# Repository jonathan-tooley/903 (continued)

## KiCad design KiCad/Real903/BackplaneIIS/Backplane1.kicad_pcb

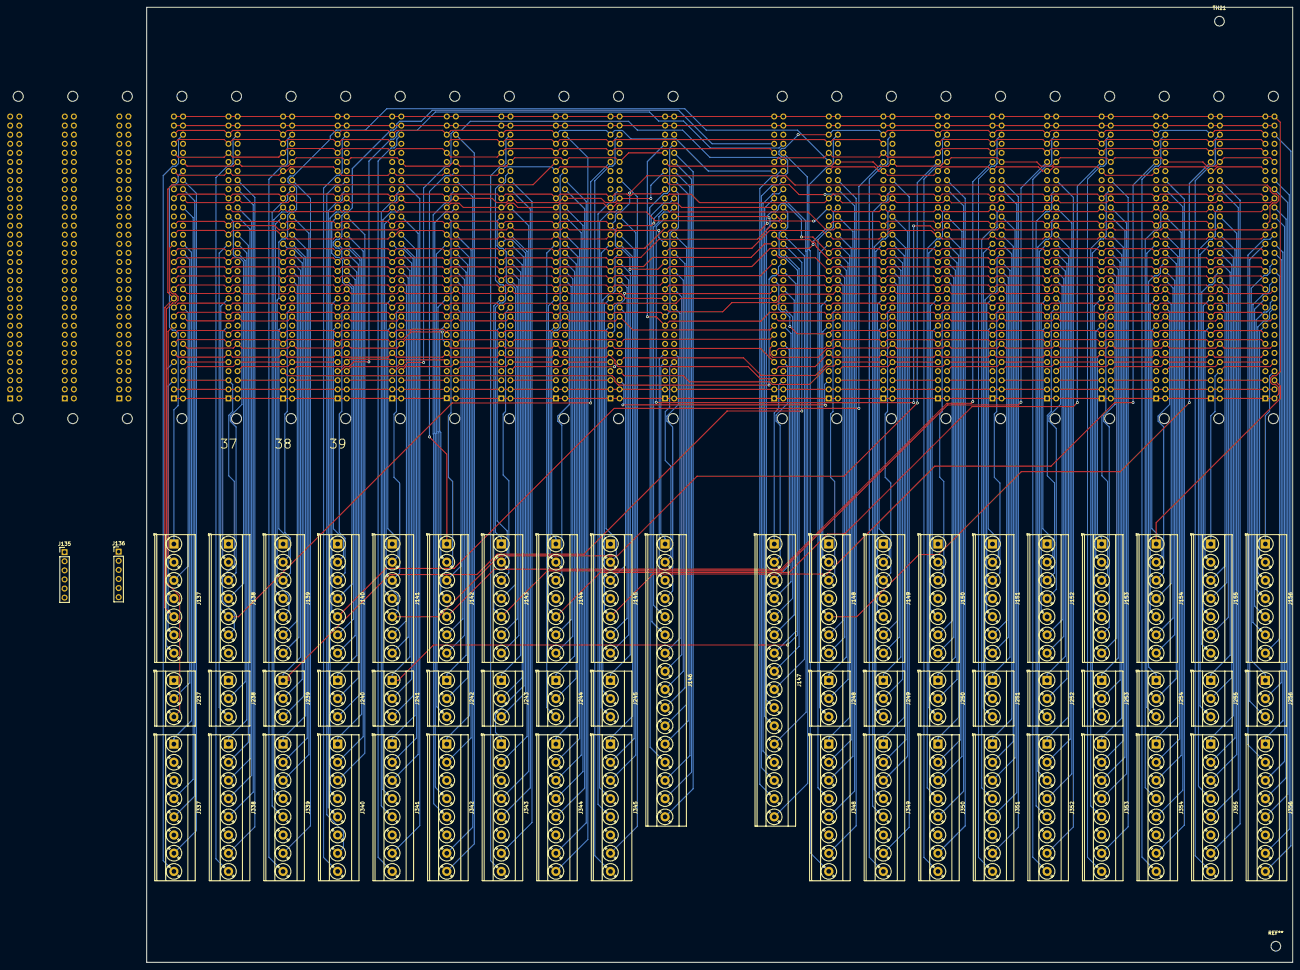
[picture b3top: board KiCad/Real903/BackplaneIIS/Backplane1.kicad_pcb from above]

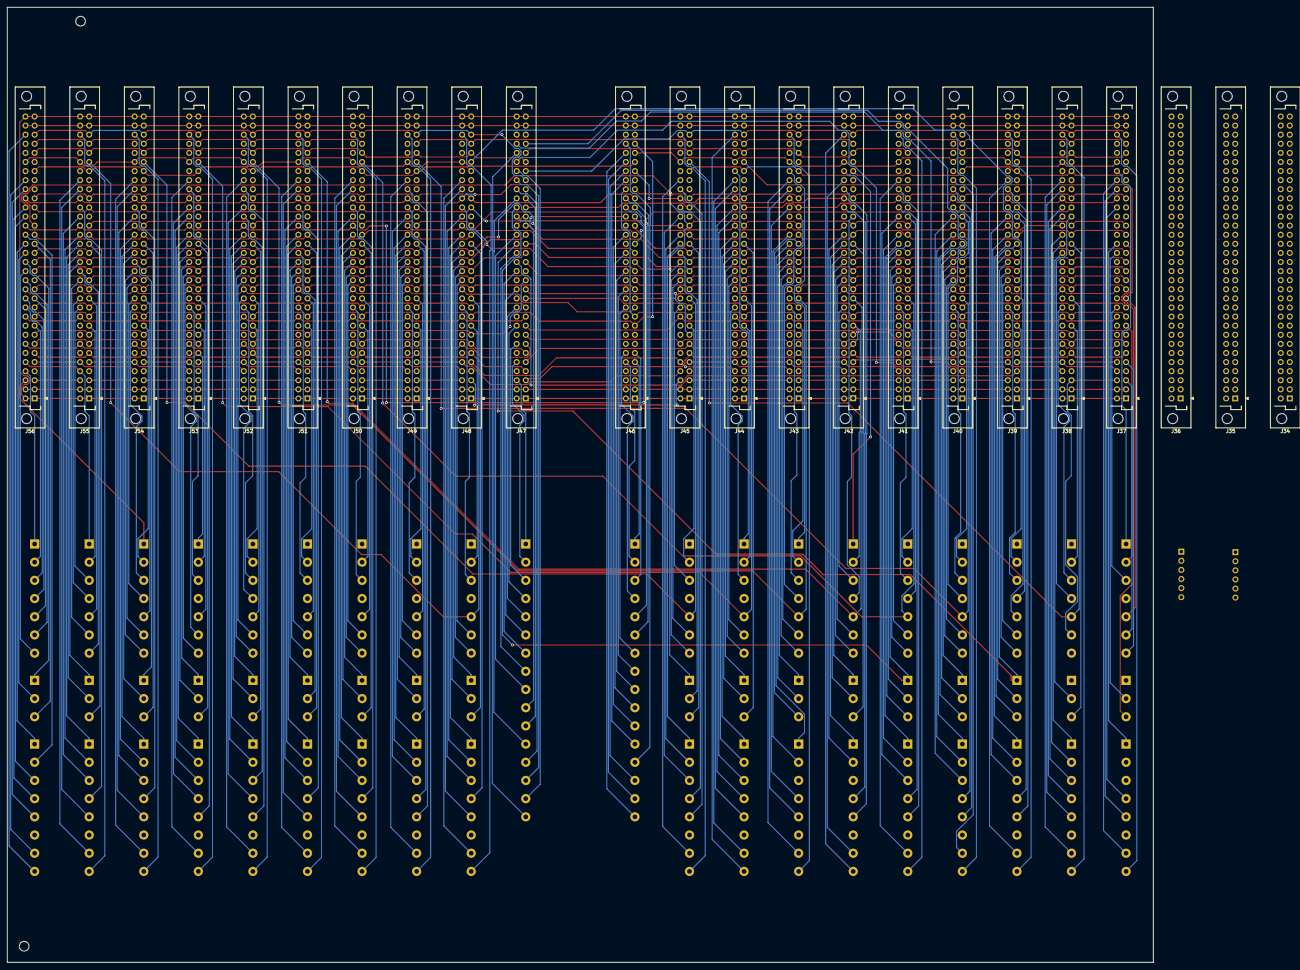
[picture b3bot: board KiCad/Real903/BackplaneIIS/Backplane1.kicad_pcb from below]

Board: 2 copper layers, 320.0 x 266.7 mm, 82 parts (23 on the bottom side), 447 nets.

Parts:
J34, J35, J36, J37, J38, J39, J40, J41, J42, J43, J44, J45, J46, J47, J48, J49, J50, J51, J52, J53, J54, J55, J56: DIN41612_B_2x32_Vertical
J135, J136: PinHeader_1x06_P2.54mm_Vertical
J137, J138, J139, J140, J141, J142, J143, J144, J145, J148, J149, J150, J151, J152, J153, J154, J155, J156: TerminalBlock_Phoenix_MKDS-3-7-5.08_1x07_P5.08mm_Horizontal
J146, J147: TerminalBlock_Phoenix_MKDS-3-16-5.08_1x16_P5.08mm_Horizontal
J237, J238, J239, J240, J241, J242, J243, J244, J245, J248, J249, J250, J251, J252, J253, J254, J255, J256: TerminalBlock_Phoenix_MKDS-3-3-5.08_1x03_P5.08mm_Horizontal
J337, J338, J339, J340, J341, J342, J343, J344, J345, J348, J349, J350, J351, J352, J353, J354, J355, J356: TerminalBlock_Phoenix_MKDS-3-8-5.08_1x08_P5.08mm_Horizontal
TH21: MountingHole_2.7mm

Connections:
0TM1-: J46.15, J48.20, J49.20, J50.20, J51.20, J52.20, J53.20, J54.20, J55.20
0TM2-: J37.20, J38.20, J39.20, J40.20, J41.20, J42.20, J43.20, J44.20, J45.20, J46.16, J56.20
6v: J34.2, J34.B, J35.2, J35.B, J36.2, J36.B, J37.2, J37.B, J38.2, J38.B, J39.2, J39.B, J40.2, J40.B, J41.2, J41.B, J42.2, J42.B, J43.2, J43.B, J44.2, J44.B, J45.2, J45.B, J46.2, J46.B, J47.2, J47.B, J48.2, J48.B, J49.2, J49.B, J50.2, J50.B, J51.2, J51.B, J52.2, J52.B, J53.2, J53.B, J54.2, J54.B, J55.2, J55.B, J56.2, J56.B
/RegistersA/C10: J44.C, J45.3
/RegistersA/C11: J43.C, J44.3
/RegistersA/C12: J42.C, J43.3
/RegistersA/C13: J41.C, J42.3
/RegistersA/C14: J40.C, J41.3
/RegistersA/C15: J39.C, J40.3
/RegistersA/C16: J38.C, J39.3
/RegistersB/C1: J55.C, J56.3
/RegistersB/C2: J54.C, J55.3
/RegistersB/C3: J53.C, J54.3
/RegistersB/C4: J52.C, J53.3
/RegistersB/C5: J51.C, J52.3
/RegistersB/C6: J50.C, J51.3
/RegistersB/C7: J49.C, J50.3
/RegistersB/C8: J48.C, J49.3
A1-: J56.AB, J356.5
A2: J48.12, J55.27, J148.5
A2-: J55.AB, J355.5
A3: J45.12, J54.27, J145.5
A3-: J54.AB, J354.5
A4: J44.12, J53.27, J144.5
A4-: J53.AB, J353.5
A5: J43.12, J52.27, J143.5
A5-: J52.AB, J352.5
A6: J42.12, J51.27, J142.5
A6-: J51.AB, J351.5
A7: J41.12, J50.27, J141.5
A7-: J50.AB, J350.5
A8: J40.12, J49.27, J140.5
A8-: J49.AB, J349.5
A9: J39.12, J48.27, J139.5
A9-: J48.AB, J348.5
A10: J38.12, J45.27, J138.5
A10-: J45.AB, J345.5
A11: J37.12, J44.27, J137.5
A11-: J44.AB, J344.5
A12-: J43.AB, J343.5
A13-: J42.AB, J342.5
A14-: J41.AB, J341.5
A15-: J40.AB, J340.5
A16-: J39.AB, J339.5
A17-: J38.AB, J338.5
A18-: J37.AB, J337.5
ATF1: J47.27, J48.28, J49.28, J50.28, J51.28, J52.28, J53.28, J54.28, J55.28, J56.28
ATF2: J37.28, J38.28, J39.28, J40.28, J41.28, J42.28, J43.28, J44.28, J45.28, J47.28
ATFa: J47.AC, J147.14
C9: J45.C, J48.3
C17: J37.C, J38.3, J138.6
C18: J37.3, J137.6
CRS: J46.5, J146.1
CRSm: J46.E, J146.2
DTF1-1: J50.29, J51.29, J52.29, J53.29, J54.29, J55.29, J56.29
DTF1-2: J42.29, J43.29, J44.29, J45.29, J48.29, J49.29
DTF2a: J37.29, J38.29, J39.29, J40.29, J41.29
ETJ2-: J55.N, J155.4
ETJ3-: J54.N, J154.4
F1: J55.D, J56.E, J155.1
F2: J54.D, J55.E, J56.5
F3: J53.D, J54.E, J55.5
F4: J52.D, J53.E, J54.5
F5: J51.D, J52.E, J53.5
F6: J50.D, J51.E, J52.5
F7: J49.D, J50.E, J51.5
F8: J48.D, J49.E, J50.5
F9: J45.D, J48.E, J49.5
F10: J44.D, J45.E, J48.5
F11: J43.D, J44.E, J45.5
F12: J42.D, J43.E, J44.5
F13: J41.D, J42.E, J43.5
F14: J40.D, J41.E, J42.5
F15: J39.D, J40.E, J41.5
F16: J38.D, J39.E, J40.5
F17: J37.D, J38.E, J39.5
F18: J37.E, J38.5
FTG1: J47.4, J48.6, J49.6, J50.6, J51.6, J52.6, J53.6, J54.6, J55.6, J56.6, J153.1
FTG2: J37.6, J38.6, J39.6, J40.6, J41.6, J42.6, J43.6, J44.6, J45.6, J47.3
FTGa: J47.C, J147.1
GND: J34.1, J34.32, J34.A, J34.AL, J35.1, J35.32, J35.A, J35.AL, J36.1, J36.32, J36.A, J36.AL, J37.1, J37.32, J37.A, J37.AL, J38.1, J38.32, J38.A, J38.AL, J39.1, J39.32, J39.A, J39.AL, J40.1, J40.32, J40.A, J40.AL, J41.1, J41.32, J41.A, J41.AL, J42.1, J42.32, J42.A, J42.AL, J43.1, J43.32, J43.A, J43.AL, J44.1, J44.32, J44.A, J44.AL, J45.1, J45.32, J45.A, J45.AL, J46.1, J46.32, J46.A, J46.AL, J47.1, J47.32, J47.A, J47.AL, J48.1, J48.32, J48.A, J48.AL, J49.1, J49.32, J49.A, J49.AL, J50.1, J50.32, J50.A, J50.AL, J51.1, J51.32, J51.A, J51.AL, J52.1, J52.32, J52.A, J52.AL, J53.1, J53.32, J53.A, J53.AL, J54.1, J54.32, J54.A, J54.AL, J55.1, J55.32, J55.A, J55.AL, J56.1, J56.32, J56.A, J56.AL
GTA1: J46.23, J48.23, J49.23, J50.23, J51.23, J52.23, J53.23, J54.23, J55.23, J56.23
GTA2: J37.23, J38.23, J39.23, J40.23, J41.23, J42.23, J43.23, J44.23, J45.23, J46.24
GTAa: J46.AA, J146.6
GTJ1: J46.13, J48.13, J49.13, J50.13, J51.13, J52.13, J53.13, J54.13, J55.13, J56.13
GTJ2: J37.13, J38.13, J39.13, J40.13, J41.13, J42.13, J43.13, J44.13, J45.13, J46.14
GTJa: J46.P, J146.8
GTM1: J46.19, J48.17, J49.17, J50.17, J51.17, J52.17, J53.17, J54.17, J55.17, J56.17
GTM2: J37.17, J38.17, J39.17, J40.17, J41.17, J42.17, J43.17, J44.17, J45.17, J46.20
GTMa: J46.W, J146.11
GTQ1: J46.27, J48.AE, J49.AE, J50.AE, J51.AE, J52.AE, J53.AE, J54.AE, J55.AE, J56.AE
GTQ2: J37.AE, J38.AE, J39.AE, J40.AE, J41.AE, J42.AE, J43.AE, J44.AE, J45.AE, J46.28
GTQa: J46.AC, J146.12
I1: J41.21, J141.4
I1-: J41.W, J341.2
I2: J40.21, J140.4
I2-: J40.W, J340.2
I3: J39.21, J139.4
I3-: J39.W, J339.2
I4: J38.21, J138.4
I4-: J38.W, J338.2
II1: J34.13, J56.25
II1m: J34.P, J35.P, J36.P
II2: J34.14, J55.25
II2m: J34.R, J35.R, J36.R
II3: J34.15, J54.25
II3m: J34.S, J35.S, J36.S
II4: J34.16, J53.25
II4m: J34.T, J35.T, J36.T
II5: J34.17, J52.25
II5m: J34.U, J35.U, J36.U
II6: J34.18, J51.25
II6m: J34.V, J35.V, J36.V
II7: J34.19, J50.25
II7m: J34.W, J35.W, J36.W
II8: J34.20, J49.25
II8m: J34.X, J35.X, J36.X
II9: J34.21, J48.25
II9m: J34.Y, J35.Y, J36.Y
II10: J34.22, J45.25
II10m: J34.Z, J35.Z, J36.Z
II11: J34.23, J44.25
II11m: J34.AA, J35.AA, J36.AA
II12: J34.24, J43.25
II12m: J34.AB, J35.AB, J36.AB
II13: J34.25, J42.25
II13m: J34.AC, J35.AC, J36.AC
II14: J34.26, J41.25
II14m: J34.AD, J35.AD, J36.AD
II15: J34.27, J40.25
II15m: J34.AE, J35.AE, J36.AE
II16: J34.28, J39.25
II16m: J34.AF, J35.AF, J36.AF
II17: J34.12, J38.25
II17m: J34.N, J35.AH, J36.AH
II18: J34.30, J37.25
II18m: J34.AJ, J35.AJ, J36.AJ
IIG: J35.26, J36.26
IIG-: J36.9, J136.2
IIS: J35.15, J36.8, J136.1
IP1: J56.9, J156.2
IP2: J55.9, J155.2
IP3: J54.9, J154.2
IP4: J53.9, J153.2
IP5: J52.9, J152.2
IP6: J51.9, J151.2
IP7: J50.9, J150.2
IP8: J49.9, J149.2
IP9: J48.9, J148.2
IP10: J45.9, J145.2
IP11: J44.9, J144.2
IP12: J43.9, J143.2
IP13: J42.9, J142.2
IP14: J41.9, J141.2
IP15: J40.9, J140.2
IP16: J39.9, J139.2
IP17: J38.9, J138.2
IP18: J37.9, J137.2
IP'1: J56.12, J156.5
IP'2: J55.12, J155.5
IP'3: J54.12, J154.5
IP'4: J53.12, J153.5
IP'5: J52.12, J152.5
IP'6: J51.12, J151.5
IP'7: J50.12, J150.5
IP'8: J49.12, J149.5
ITF: J56.C, J154.1
J1: J56.T, J256.1
J1': J35.7, J36.7, J135.2
J1-: J56.R, J156.6
J1-': J35.8, J135.1
J2: J55.T, J255.1
J2': J35.9, J135.4
J2-: J55.R, J155.6
J2-': J35.10, J36.10, J135.3
J3: J54.T, J254.1
J3': J35.11, J36.11, J135.6
J3-: J54.R, J154.6
J3-': J35.12, J36.C, J135.5
J4: J35.14, J53.T, J253.1
J4-: J35.13, J36.12, J53.R, J153.6
J5: J36.13, J52.T, J252.1
J5-: J52.R, J152.6
J6: J36.14, J51.T, J251.1
J6-: J51.R, J151.6
J7: J36.15, J50.T, J250.1
J7-: J50.R, J150.6
J8: J36.18, J49.T, J249.1
J8-: J49.R, J149.6
J9: J36.19, J48.T, J248.1
J9-: J48.R, J148.6
J10: J36.20, J45.T, J245.1
J10-: J45.R, J145.6
J11: J36.21, J44.T, J244.1
J11-: J44.R, J144.6
J12: J36.22, J43.T, J243.1
J12-: J43.R, J143.6
J13: J36.23, J42.T, J242.1
J13-: J42.R, J142.6
J14: J41.T, J47.Z, J241.1
J14-: J36.24, J41.R, J141.6
J15: J40.T, J47.29, J240.1
J15-: J36.25, J40.R, J140.6
J16: J39.T, J47.V, J239.1
J16-: J36.29, J39.R, J139.6
JTF1: J47.15, J48.14, J49.14, J50.14, J51.14, J52.14, J53.14, J54.14, J55.14, J56.14
JTF2: J37.14, J38.14, J39.14, J40.14, J41.14, J42.14, J43.14, J44.14, J45.14, J47.16
JTFa: J47.S, J147.7
JTG14-: J41.4, J47.AE
JTG15-: J40.4, J47.AH
JTG16-: J39.4, J47.T
JTPC: J47.23, J47.24, J147.11
JTPCa: J47.AA, J147.12
KTJ1-: J56.N, J156.4
KTJ5-: J52.N, J152.4
LTG1: J47.7, J48.H, J49.H, J50.H, J51.H, J52.H, J53.H, J54.H, J55.H, J56.H
LTG2: J37.H, J38.H, J39.H, J40.H, J41.H, J42.H, J43.H, J44.H, J45.H, J47.8
LTGa: J47.H, J147.3
M1-: J56.V, J356.1
M2-: J55.V, J355.1
M3-: J54.V, J354.1
M4-: J53.V, J353.1
M5-: J52.V, J352.1
M6-: J51.V, J351.1
M7-: J50.V, J350.1
M8-: J49.V, J349.1
M9-: J48.V, J348.1
M10-: J45.V, J345.1
M11: J44.AD, J144.1
M11-: J44.V, J344.1
M12: J43.AD, J143.1
M12-: J43.V, J343.1
M13: J42.AD, J142.1
M13-: J42.V, J342.1
M14-: J41.V, J341.1
M15-: J40.V, J340.1
M16-: J39.V, J339.1
M17-: J38.V, J338.1
M18: J37.AD, J137.1
M18-: J37.V, J337.1
M-TF1: J47.19, J48.16, J49.16, J50.16, J51.16, J52.16, J53.16, J54.16, J55.16, J56.16
M-TF2: J37.16, J38.16, J39.16, J40.16, J41.16, J42.16, J43.16, J44.16, J45.16, J47.20
M-TFa: J47.W, J147.9
MTF1: J47.17, J48.15, J49.15, J50.15, J51.15, J52.15, J53.15, J54.15, J55.15, J56.15
MTF2: J37.15, J38.15, J39.15, J40.15, J41.15, J42.15, J43.15, J44.15, J45.15, J47.18
MTFa: J47.U, J147.8
MTI: J38.22, J39.22, J40.22, J41.22, J47.X
MTP1: J47.21, J48.22, J49.22, J50.22, J51.22, J52.22, J53.22, J54.22, J55.22, J56.22
MTP2: J42.22, J43.22, J44.22, J45.22, J47.22
MTPa: J46.Y, J47.Y, J147.10
Neg6v: J34.31, J34.AK, J35.31, J35.AK, J36.31, J36.AK, J37.31, J37.AK, J38.31, J38.AK, J39.31, J39.AK, J40.31, J40.AK, J41.31, J41.AK, J42.31, J42.AK, J43.31, J43.AK, J44.31, J44.AK, J45.31, J45.AK, J46.31, J46.AK, J47.31, J47.AK, J48.31, J48.AK, J49.31, J49.AK, J50.31, J50.AK, J51.31, J51.AK, J52.31, J52.AK, J53.31, J53.AK, J54.31, J54.AK, J55.31, J55.AK, J56.31, J56.AK
OTA1-: J46.25, J48.AA, J49.AA, J50.AA, J51.AA, J52.AA, J53.AA, J54.AA, J55.AA, J56.AA
OTA2-: J37.AA, J38.AA, J39.AA, J40.AA, J41.AA, J42.AA, J43.AA, J44.AA, J45.AA, J46.26
OTA-': J46.Z, J146.5
OTG1-: J46.9, J46.29, J48.10, J49.10, J50.10, J51.10, J52.10, J53.10, J54.10, J55.10, J56.10
OTG2-: J37.10, J38.10, J39.10, J40.10, J41.10, J42.10, J43.10, J44.10, J45.10, J46.10, J46.AB
OTI-: J38.X, J39.X, J40.X, J41.X
OTJ1-: J46.11, J48.P, J49.P, J50.P, J51.P, J52.P, J53.P, J54.P, J55.P, J56.P
OTJ2-: J37.P, J38.P, J39.P, J40.P, J41.P, J42.P, J43.P, J44.P, J45.P, J46.12
OTJ-: J46.M, J146.7
OTMa: J46.S, J146.9
OTP1-: J46.21, J50.X, J51.X, J52.X, J53.X, J54.X, J55.X, J56.X
OTP2-: J42.X, J43.X, J44.X, J45.X, J46.22, J48.X, J49.X
OTQ1-: J48.26, J49.26, J50.26, J51.26, J52.26, J53.26, J54.26, J55.26, J56.26
OTQ2-: J37.26, J38.26, J39.26, J40.26, J41.26, J42.26, J43.26, J44.26, J45.26
P1-: J56.W, J356.2
P2-: J55.W, J355.2
P3-: J54.W, J354.2
P4-: J53.W, J353.2
P5-: J52.W, J352.2
P6-: J51.W, J351.2
P7-: J50.W, J350.2
P8-: J49.W, J349.2
P9-: J48.W, J348.2
P10-: J45.W, J345.2
P11-: J44.W, J344.2
P12: J43.21, J143.4
P12-: J43.W, J343.2
P13: J42.21, J142.4
P13-: J42.W, J342.2
PTG1-1: J47.10, J48.L, J49.L, J50.L, J51.L, J52.L, J53.L, J54.L, J55.L, J56.L
PTG1-2: J37.L, J38.L, J39.L, J40.L, J41.L, J42.L, J43.L, J44.L, J45.L, J47.9
PTG1-a: J47.K, J147.4
PTG2-1: J47.11, J48.11, J49.11, J50.11, J51.11, J52.11, J53.11, J54.11, J55.11, J56.11
PTG2-2: J37.11, J38.11, J39.11, J40.11, J41.11, J42.11, J43.11, J44.11, J45.11, J47.12
PTG2-a: J47.M, J147.5
QTF1: J47.25, J48.30, J49.30, J50.30, J51.30, J52.30, J53.30, J54.30, J55.30, J56.30
QTF2: J37.30, J38.30, J39.30, J40.30, J41.30, J42.30, J43.30, J44.30, J45.30, J47.26
QTFa: J47.AB, J147.13
RESET2-: J46.AH, J146.13
RTG1: J47.6, J48.7, J49.7, J50.7, J51.7, J52.7, J53.7, J54.7, J55.7, J56.7
RTG2: J37.7, J38.7, J39.7, J40.7, J41.7, J42.7, J43.7, J44.7, J45.7, J47.5
RTGa: J47.E, J147.2
SFD: J46.6, J146.3
SFDm: J46.F, J146.4
SKT1AA: J44.AC, J344.7
SKT1B: J56.M, J156.3
SKT1BB: J43.AC, J343.7
SKT1C: J55.M, J155.3
SKT1CC: J42.AC, J342.7
SKT1D: J54.M, J154.3
SKT1DD: J41.AC, J341.7
SKT1E: J53.M, J153.3
SKT1EE: J40.AC, J340.7
SKT1F: J52.M, J152.3
SKT1FF: J39.AC, J339.7
SKT1G: J51.M, J151.3
SKT1GG: J38.AC, J338.7
SKT1H: J50.M, J150.3
SKT1HH: J37.AC, J337.7
SKT1J: J49.M, J149.3
SKT1K: J48.M, J148.3
SKT1L: J45.M, J145.3
SKT1M: J44.M, J144.3
SKT1N: J43.M, J143.3
SKT1P: J42.M, J142.3
SKT1R: J41.M, J141.3
SKT1S: J40.M, J140.3
SKT1T: J39.M, J139.3
SKT1U: J38.M, J138.3
SKT1V: J37.M, J137.3
SKT1W: J56.Z, J356.4
SKT1X: J55.Z, J355.4
SKT1Y: J54.Z, J354.4
SKT1Z: J53.Z, J353.4
SKT1a: J52.Z, J352.4
SKT1b_: J51.Z, J351.4
SKT1c_: J50.Z, J350.4
SKT1d_: J49.Z, J349.4
SKT1e_: J48.Z, J348.4
SKT1f_: J45.Z, J345.4
SKT1g_: J44.Z, J344.4
SKT1h_: J43.Z, J343.4
SKT1i: J42.Z, J342.4
SKT1j_: J41.Z, J341.4
SKT1k_: J40.Z, J340.4
SKT1m_: J39.Z, J339.4
SKT1n_: J38.Z, J338.4
SKT1p_: J37.Z, J337.4
SKT1q: J56.AC, J356.7
SKT1r_: J55.AC, J355.7
SKT1s_: J54.AC, J354.7
SKT1t_: J53.AC, J353.7
SKT1u_: J52.AC, J352.7
SKT1v_: J51.AC, J351.7
SKT1w_: J50.AC, J350.7
SKT1x_: J49.AC, J349.7
SKT1y_: J48.AC, J348.7
SKT1z_: J45.AC, J345.7
SKT2B: J56.U, J256.2
SKT2C: J55.U, J255.2
SKT2D: J54.U, J254.2
SKT2E: J53.U, J253.2
SKT2F: J52.U, J252.2
SKT2G: J51.U, J251.2
SKT2H: J50.U, J250.2
SKT2J: J49.U, J249.2
SKT2K: J48.U, J248.2
SKT2L: J45.U, J245.2
SKT2M: J44.U, J244.2
SKT2N: J43.U, J243.2
SKT2P: J42.U, J242.2
SKT2R: J41.U, J241.2
SKT2S: J40.U, J240.2
SKT2T: J39.U, J239.2
SKT2U: J38.U, J238.2
SKT2V: J37.U, J237.2
SKT2W: J56.S, J156.7
SKT2X: J55.S, J155.7
SKT2Y: J54.S, J154.7
SKT2Z: J53.S, J153.7
SKT2a: J52.S, J152.7
SKT2b_: J51.S, J151.7
SKT2c_: J50.S, J150.7
SKT2d_: J49.S, J149.7
SKT2e_: J48.S, J148.7
SKT2f_: J45.S, J145.7
SKT2g_: J44.S, J144.7
SKT2h_: J43.S, J143.7
SKT2i: J42.S, J142.7
SKT2j_: J41.S, J141.7
SKT2k_: J40.S, J140.7
SKT2m_: J39.S, J139.7
SKT2n_: J56.Y, J356.3
SKT2p_: J55.Y, J355.3
SKT2q: J54.Y, J354.3
SKT2r_: J53.Y, J353.3
SKT2s_: J52.Y, J352.3
SKT2t_: J51.Y, J351.3
SKT2u_: J50.Y, J350.3
SKT2v_: J49.Y, J349.3
SKT2w_: J48.Y, J348.3
SKT2x_: J45.Y, J345.3
SKT2y_: J44.Y, J344.3
SKT3r: J41.Y, J341.3
SKT3s: J40.Y, J340.3
SKT3t: J39.Y, J339.3
SKT3u: J38.Y, J338.3
SKT11B: J56.18, J256.3
SKT11F: J52.18, J252.3
SKT11G: J51.18, J251.3
SKT11H: J50.18, J250.3
SKT11J: J49.18, J249.3
SKT11K: J48.18, J248.3
SKT11L: J45.18, J245.3
SKT11M: J44.18, J244.3
SKT11N: J43.18, J243.3
SKT11P: J42.18, J242.3
STORE1-: J56.AJ, J356.8
STORE2-: J55.AJ, J355.8
STORE3-: J54.AJ, J354.8
STORE4-: J53.AJ, J353.8
STORE5-: J52.AJ, J352.8
STORE6-: J51.AJ, J351.8
STORE7-: J50.AJ, J350.8
STORE8-: J49.AJ, J349.8
STORE9-: J48.AJ, J348.8
STORE10-: J45.AJ, J345.8
STORE11-: J44.AJ, J344.8
STORE12-: J43.AJ, J343.8
STORE13-: J42.AJ, J342.8
STORE14-: J41.AJ, J341.8
STORE15-: J40.AJ, J340.8
STORE16-: J39.AJ, J339.8
STORE17-: J38.AJ, J338.8
STORE18-: J37.AJ, J337.8
VTG1: J47.14, J48.8, J49.8, J50.8, J51.8, J52.8, J53.8, J54.8, J55.8, J56.8
VTG2: J37.8, J38.8, J39.8, J40.8, J41.8, J42.8, J43.8, J44.8, J45.8, J47.13
VTGa: J47.P, J147.6
W2: J55.18, J255.3
W3: J54.18, J254.3
W4: J53.18, J253.3
W14: J41.18, J241.3
W15: J40.18, J240.3
W16: J39.18, J239.3
W17: J38.18, J238.3
W18: J37.18, J237.3
WTM1: J46.17, J48.19, J49.19, J50.19, J51.19, J52.19, J53.19, J54.19, J55.19, J56.19
WTM2: J37.19, J38.19, J39.19, J40.19, J41.19, J42.19, J43.19, J44.19, J45.19, J46.18
WTMa: J46.U, J146.10
X0: J56.D, J156.1
X1: J37.5, J137.7
t1: J46.AF, J146.16
t2-2: J47.AF, J147.16
t3-2: J46.AE, J146.15
t4: J46.AD, J146.14
t5: J47.AD, J147.15

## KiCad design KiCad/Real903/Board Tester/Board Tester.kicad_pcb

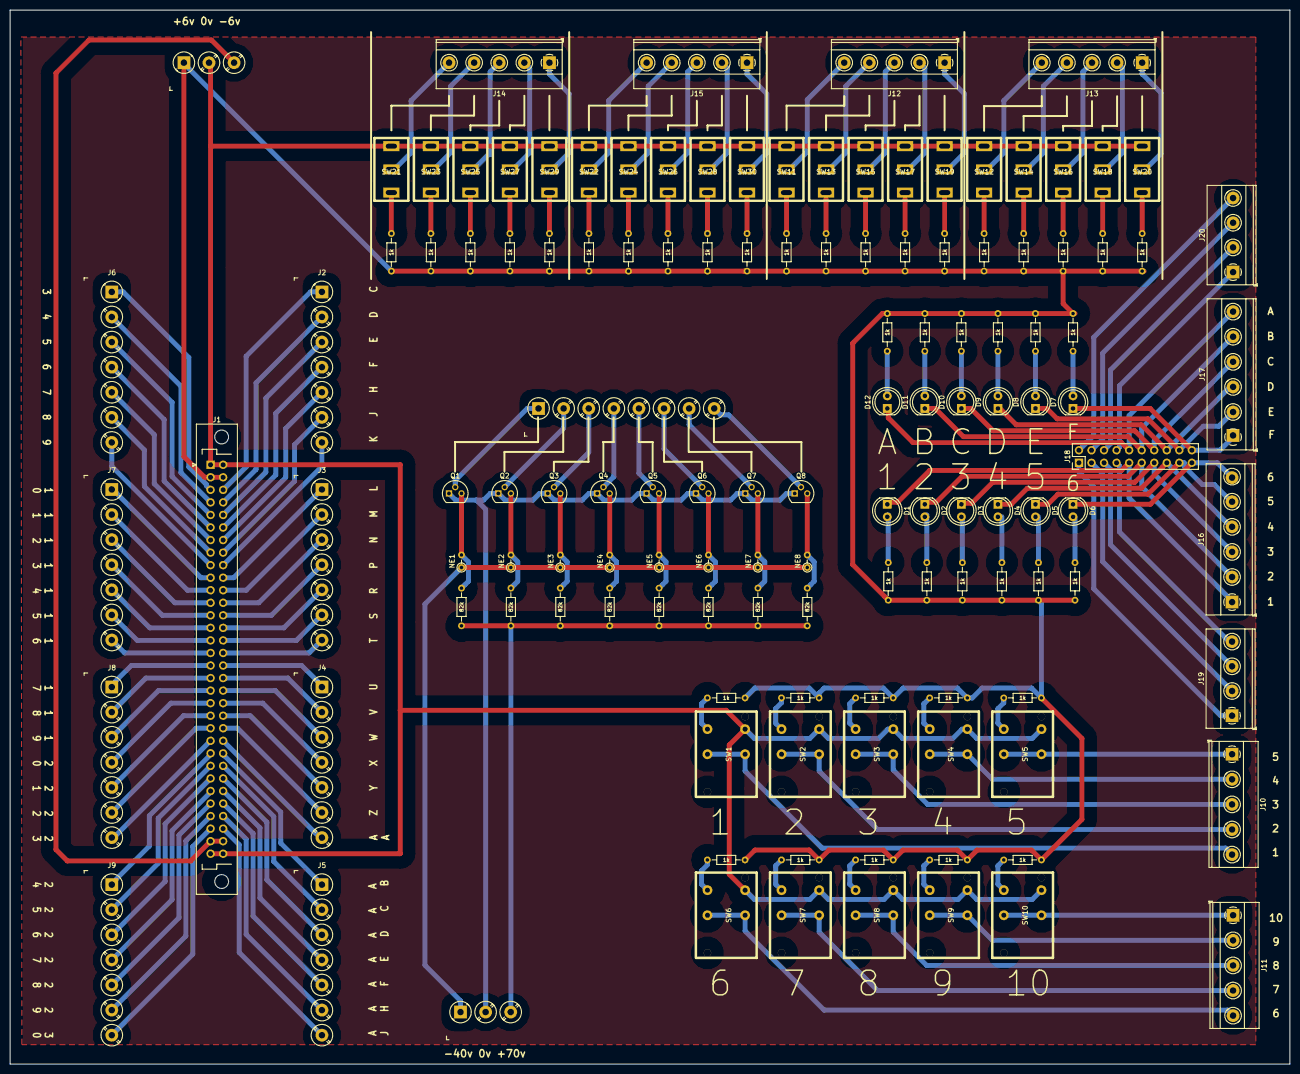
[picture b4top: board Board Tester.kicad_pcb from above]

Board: 2 copper layers, 259.1 x 213.4 mm, 131 parts (0 on the bottom side), 170 nets.

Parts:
D1, D2, D3, D4, D5, D6, D7, D8, D9, D10, D11, D12: LED_D5.0mm
J0: Conn_01x03; TerminalBlock_5.08_1x03
J1: DIN41612_B_2x32_Vertical
J2, J3, J4, J5, J6, J7, J8, J9: TerminalBlock_5.08_1x07
J10, J11, J12, J13, J14, J15: TerminalBlock_Phoenix_MKDS-1,5-5-5.08_1x05_P5.08mm_Horizont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
J16, J17: TerminalBlock_Phoenix_MKDS-1,5-6-5.08_1x06_P5.08mm_Horizont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
J18: PinHeader_2x10_P2.54mm_Vertical
J19, J20: TerminalBlock_Phoenix_MKDS-1,5-4_1x04_P5.00mm_Horizontal
J21: TerminalBlock_5.08_1x08
J22: TerminalBlock_5.08_1x03
NE1, NE2, NE3, NE4, NE5, NE6, NE7, NE8: R_Axial_DIN0204_L3.6mm_D1.6mm_P2.54mm_Vertical
Q1, Q2, Q3, Q4, Q5, Q6, Q7, Q8: TO-92
R1, R2, R3, R4, R5, R6, R7, R8, R9, R10, R11, R12, R13, R14, R15, R16, R17, R18, R19, R20, R21, R22, R23, R24, R25, R26, R27, R28, R29, R30, R31, R32, R33, R34, R35, R36, R37, R38, R39, R40, R41, R42: 1k; R_Axial_DIN0204_L3.6mm_D1.6mm_P7.62mm_Horizontal
R43, R44, R45, R46, R47, R48, R49, R50: 82k; R_Axial_DIN0204_L3.6mm_D1.6mm_P7.62mm_Horizontal
SW1, SW2, SW3, SW4, SW5, SW6, SW7, SW8, SW9, SW10: KeyPush
SW11, SW12, SW13, SW14, SW15, SW16, SW17, SW18, SW19, SW20, SW21, SW22, SW23, SW24, SW25, SW26, SW27, SW28, SW29, SW30: MiniSPDTSwitch

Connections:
0v: J22.2, Q1.1, Q2.1, Q3.1, Q4.1, Q5.1, Q6.1, Q7.1, Q8.1
+6v: J0.1, J1.2, J1.B, R1.1, R2.1, R3.1, R4.1, R5.1, R6.1, R7.1, R8.1, R9.1, R10.1, R11.1, R12.1, R13.1, R14.1, R15.1, R16.1, R17.1, R18.1, R19.1, R20.1, R21.1, R22.1, R23.1, R24.1, R25.1, R26.1, R27.1, R28.1, R29.1, R30.1, R31.2, R32.2, R33.2, R34.2, R35.2, R36.2, R37.2, R38.2, R39.2, R40.2, R41.2, R42.2
+70v: J22.3, R43.1, R44.1, R45.1, R46.1, R47.1, R48.1, R49.1, R50.1
-6v: J0.3, J1.31, J1.AK
-40v: J22.1, NE1.1, NE2.1, NE3.1, NE4.1, NE5.1, NE6.1, NE7.1, NE8.1
GND: J0.2, J1.1, J1.32, J1.A, J1.AL, SW1.3, SW2.3, SW3.3, SW4.3, SW5.3, SW6.3, SW7.3, SW8.3, SW9.3, SW10.3, SW11.3, SW12.3, SW13.3, SW14.3, SW15.3, SW16.3, SW17.3, SW18.3, SW19.3, SW20.3, SW21.3, SW22.3, SW23.3, SW24.3, SW25.3, SW26.3, SW27.3, SW28.3, SW29.3, SW30.3
unnamed: D1.1, J16.1, J18.9
unnamed: D1.2, R31.1
unnamed: D2.1, J16.2, J18.11
unnamed: D2.2, R32.1
unnamed: D3.1, J16.3, J18.13
unnamed: D3.2, R33.1
unnamed: D4.1, J16.4, J18.15
unnamed: D4.2, R34.1
unnamed: D5.1, J16.5, J18.17
unnamed: D5.2, R35.1
unnamed: D6.1, J16.6, J18.19
unnamed: D6.2, R36.1
unnamed: D7.1, J17.1, J18.20
unnamed: D7.2, R37.1
unnamed: D8.1, J17.2, J18.18
unnamed: D8.2, R38.1
unnamed: D9.1, J17.3, J18.16
unnamed: D9.2, R39.1
unnamed: D10.1, J17.4, J18.14
unnamed: D10.2, R40.1
unnamed: D11.1, J17.5, J18.12
unnamed: D11.2, R41.1
unnamed: D12.1, J17.6, J18.10
unnamed: D12.2, R42.1
unnamed: J1.3, J6.1
unnamed: J1.4, J6.2
unnamed: J1.5, J6.3
unnamed: J1.6, J6.4
unnamed: J1.7, J6.5
unnamed: J1.8, J6.6
unnamed: J1.9, J6.7
unnamed: J1.10, J7.1
unnamed: J1.11, J7.2
unnamed: J1.12, J7.3
unnamed: J1.13, J7.4
unnamed: J1.14, J7.5
unnamed: J1.15, J7.6
unnamed: J1.16, J7.7
unnamed: J1.17, J8.1
unnamed: J1.18, J8.2
unnamed: J1.19, J8.3
unnamed: J1.20, J8.4
unnamed: J1.21, J8.5
unnamed: J1.22, J8.6
unnamed: J1.23, J8.7
unnamed: J1.24, J9.1
unnamed: J1.25, J9.2
unnamed: J1.26, J9.3
unnamed: J1.27, J9.4
unnamed: J1.28, J9.5
unnamed: J1.29, J9.6
unnamed: J1.30, J9.7
unnamed: J1.AA, J4.7
unnamed: J1.AB, J5.1
unnamed: J1.AC, J5.2
unnamed: J1.AD, J5.3
unnamed: J1.AE, J5.4
unnamed: J1.AF, J5.5
unnamed: J1.AH, J5.6
unnamed: J1.AJ, J5.7
unnamed: J1.C, J2.1
unnamed: J1.D, J2.2
unnamed: J1.E, J2.3
unnamed: J1.F, J2.4
unnamed: J1.H, J2.5
unnamed: J1.J, J2.6
unnamed: J1.K, J2.7
unnamed: J1.L, J3.1
unnamed: J1.M, J3.2
unnamed: J1.N, J3.3
unnamed: J1.P, J3.4
unnamed: J1.R, J3.5
unnamed: J1.S, J3.6
unnamed: J1.T, J3.7
unnamed: J1.U, J4.1
unnamed: J1.V, J4.2
unnamed: J1.W, J4.3
unnamed: J1.X, J4.4
unnamed: J1.Y, J4.5
unnamed: J1.Z, J4.6
unnamed: J10.1, SW5.2
unnamed: J10.2, SW4.2
unnamed: J10.3, SW3.2
unnamed: J10.4, SW2.2
unnamed: J10.5, SW1.2
unnamed: J11.1, SW10.2
unnamed: J11.2, SW9.2
unnamed: J11.3, SW8.2
unnamed: J11.4, SW7.2
unnamed: J11.5, SW6.2
unnamed: J12.1, SW19.2
unnamed: J12.2, SW17.2
unnamed: J12.3, SW15.2
unnamed: J12.4, SW13.2
unnamed: J12.5, SW11.2
unnamed: J13.1, SW20.2
unnamed: J13.2, SW18.2
unnamed: J13.3, SW16.2
unnamed: J13.4, SW14.2
unnamed: J13.5, SW12.2
unnamed: J14.1, SW29.2
unnamed: J14.2, SW27.2
unnamed: J14.3, SW25.2
unnamed: J14.4, SW23.2
unnamed: J14.5, SW21.2
unnamed: J15.1, SW30.2
unnamed: J15.2, SW28.2
unnamed: J15.3, SW26.2
unnamed: J15.4, SW24.2
unnamed: J15.5, SW22.2
unnamed: J18.1, J19.1
unnamed: J18.2, J20.4
unnamed: J18.3, J19.2
unnamed: J18.4, J20.3
unnamed: J18.5, J19.3
unnamed: J18.6, J20.2
unnamed: J18.7, J19.4
unnamed: J18.8, J20.1
unnamed: J21.1, Q1.2
unnamed: J21.2, Q2.2
unnamed: J21.3, Q3.2
unnamed: J21.4, Q4.2
unnamed: J21.5, Q5.2
unnamed: J21.6, Q6.2
unnamed: J21.7, Q7.2
unnamed: J21.8, Q8.2
unnamed: NE1.2, Q1.3, R43.2
unnamed: NE2.2, Q2.3, R44.2
unnamed: NE3.2, Q3.3, R45.2
unnamed: NE4.2, Q4.3, R46.2
unnamed: NE5.2, Q5.3, R47.2
unnamed: NE6.2, Q6.3, R48.2
unnamed: NE7.2, Q7.3, R49.2
unnamed: NE8.2, Q8.3, R50.2
unnamed: R1.2, SW1.1
unnamed: R2.2, SW2.1
unnamed: R3.2, SW3.1
unnamed: R4.2, SW4.1
unnamed: R5.2, SW5.1
unnamed: R6.2, SW6.1
unnamed: R7.2, SW7.1
unnamed: R8.2, SW8.1
unnamed: R9.2, SW9.1
unnamed: R10.2, SW10.1
unnamed: R11.2, SW11.1
unnamed: R12.2, SW12.1
unnamed: R13.2, SW13.1
unnamed: R14.2, SW14.1
unnamed: R15.2, SW15.1
unnamed: R16.2, SW16.1
unnamed: R17.2, SW17.1
unnamed: R18.2, SW18.1
unnamed: R19.2, SW19.1
unnamed: R20.2, SW20.1
unnamed: R21.2, SW21.1
unnamed: R22.2, SW22.1
unnamed: R23.2, SW23.1
unnamed: R24.2, SW24.1
unnamed: R25.2, SW25.1
unnamed: R26.2, SW26.1
unnamed: R27.2, SW27.1
unnamed: R28.2, SW28.1
unnamed: R29.2, SW29.1
unnamed: R30.2, SW30.1

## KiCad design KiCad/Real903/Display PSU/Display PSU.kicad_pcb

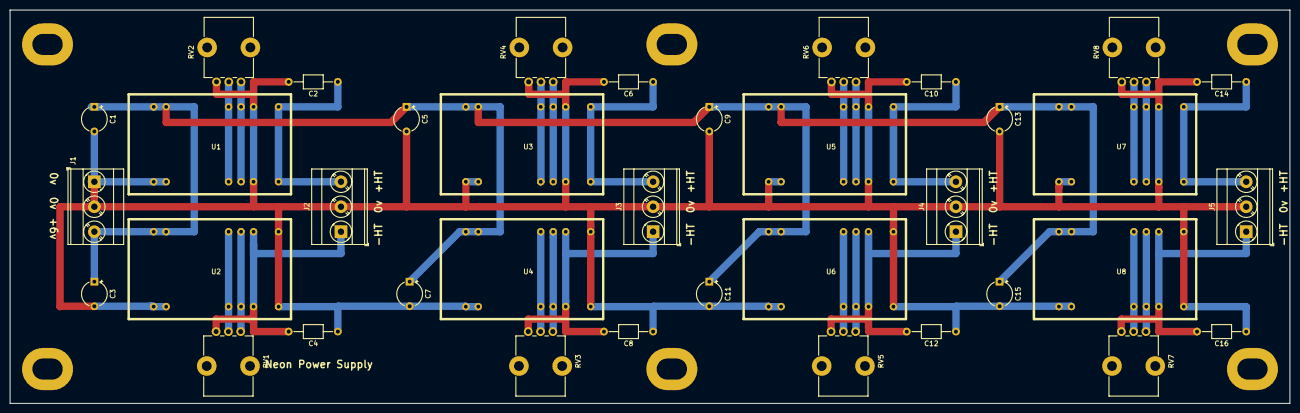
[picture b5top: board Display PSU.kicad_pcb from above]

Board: 2 copper layers, 260.4 x 80.0 mm, 43 parts (0 on the bottom side), 26 nets.

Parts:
C1, C3, C5, C7, C9, C11, C13, C15: 47u; CP_Radial_Tantal_D5.0mm_P5.00mm
C2, C4, C6, C8, C10, C12, C14, C16: 4700pf 250v; C_Axial_L3.8mm_D2.6mm_P10.00mm_Horizontal
H1, H2, H3, H4, H5, H6: MountingHole_4.3x6.2mm_M4_Pad
J1, J2, J3, J4, J5: TerminalBlock_Phoenix_MKDS-3-3-5.08_1x03_P5.08mm_Horizontal
RV1, RV2, RV3, RV4, RV5, RV6, RV7, RV8: 5k; Potentiometer_Alps_RK09K_Single_Vertical
U1, U2, U3, U4, U5, U6, U7, U8: R05-100B

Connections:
0v: C1.2, C2.2, C3.2, C4.1, C5.2, C6.2, C7.2, C8.1, C9.2, C10.2, C11.2, C12.1, C13.2, C14.2, C15.2, C16.1, J1.1, J1.2, J2.2, J3.2, J4.2, J5.2, RV2.3, RV4.3, RV6.3, RV8.3, U1.2, U1.3, U1.10, U1.15, U2.2, U2.3, U2.12, U2.13, U3.2, U3.3, U3.10, U3.15, U4.2, U4.3, U4.12, U4.13, U5.2, U5.3, U5.10, U5.15, U6.2, U6.3, U6.12, U6.13, U7.2, U7.3, U7.10, U7.15, U8.2, U8.3, U8.12, U8.13
+6v: C1.1, C3.1, C5.1, C7.1, C9.1, C11.1, C13.1, C15.1, J1.3, U1.22, U1.23, U2.22, U2.23, U3.22, U3.23, U4.22, U4.23, U5.22, U5.23, U6.22, U6.23, U7.22, U7.23, U8.22, U8.23
+HT1: C2.1, J2.3, U1.12, U1.13
+HT2: C6.1, J3.3, U3.12, U3.13
+HT3: C10.1, J4.3, U5.12, U5.13
+HT4: C14.1, J5.3, U7.12, U7.13
-HT1: C4.2, J2.1, RV1.1, U2.10, U2.15
-HT2: C8.2, J3.1, RV3.1, U4.10, U4.15
-HT3: C12.2, J4.1, RV5.1, U6.10, U6.15
-HT4: C16.2, J5.1, RV7.1, U8.10, U8.15
unnamed: RV1.2, U2.8, U2.17
unnamed: RV1.3, U2.9, U2.16
unnamed: RV2.1, U1.9, U1.16
unnamed: RV2.2, U1.8, U1.17
unnamed: RV3.2, U4.8, U4.17
unnamed: RV3.3, U4.9, U4.16
unnamed: RV4.1, U3.9, U3.16
unnamed: RV4.2, U3.8, U3.17
unnamed: RV5.2, U6.8, U6.17
unnamed: RV5.3, U6.9, U6.16
unnamed: RV6.1, U5.9, U5.16
unnamed: RV6.2, U5.8, U5.17
unnamed: RV7.2, U8.8, U8.17
unnamed: RV7.3, U8.9, U8.16
unnamed: RV8.1, U7.9, U7.16
unnamed: RV8.2, U7.8, U7.17
